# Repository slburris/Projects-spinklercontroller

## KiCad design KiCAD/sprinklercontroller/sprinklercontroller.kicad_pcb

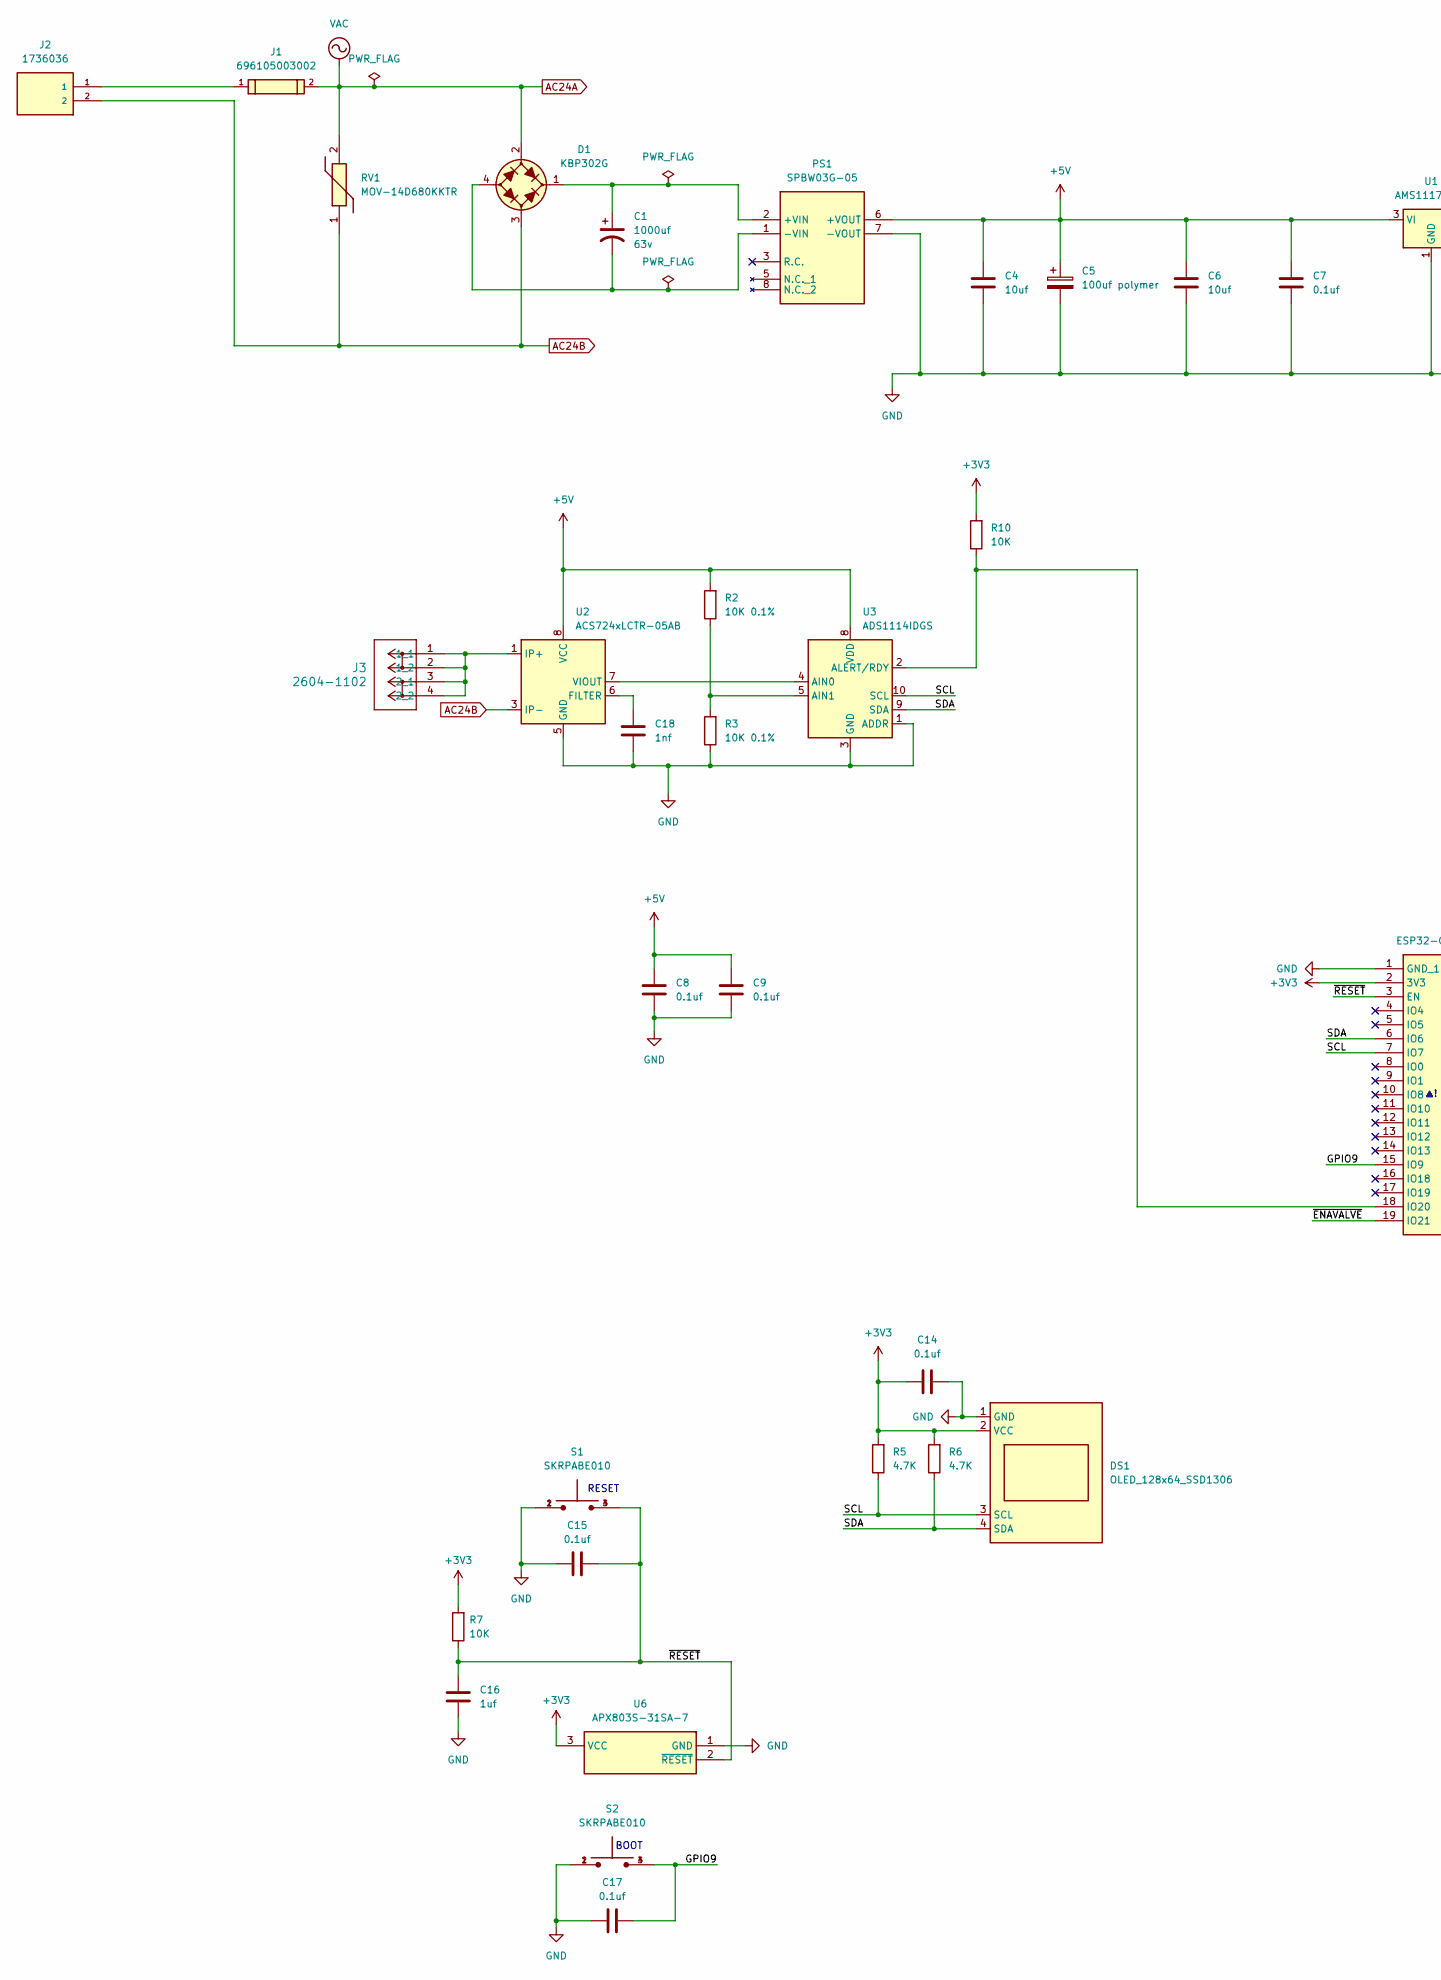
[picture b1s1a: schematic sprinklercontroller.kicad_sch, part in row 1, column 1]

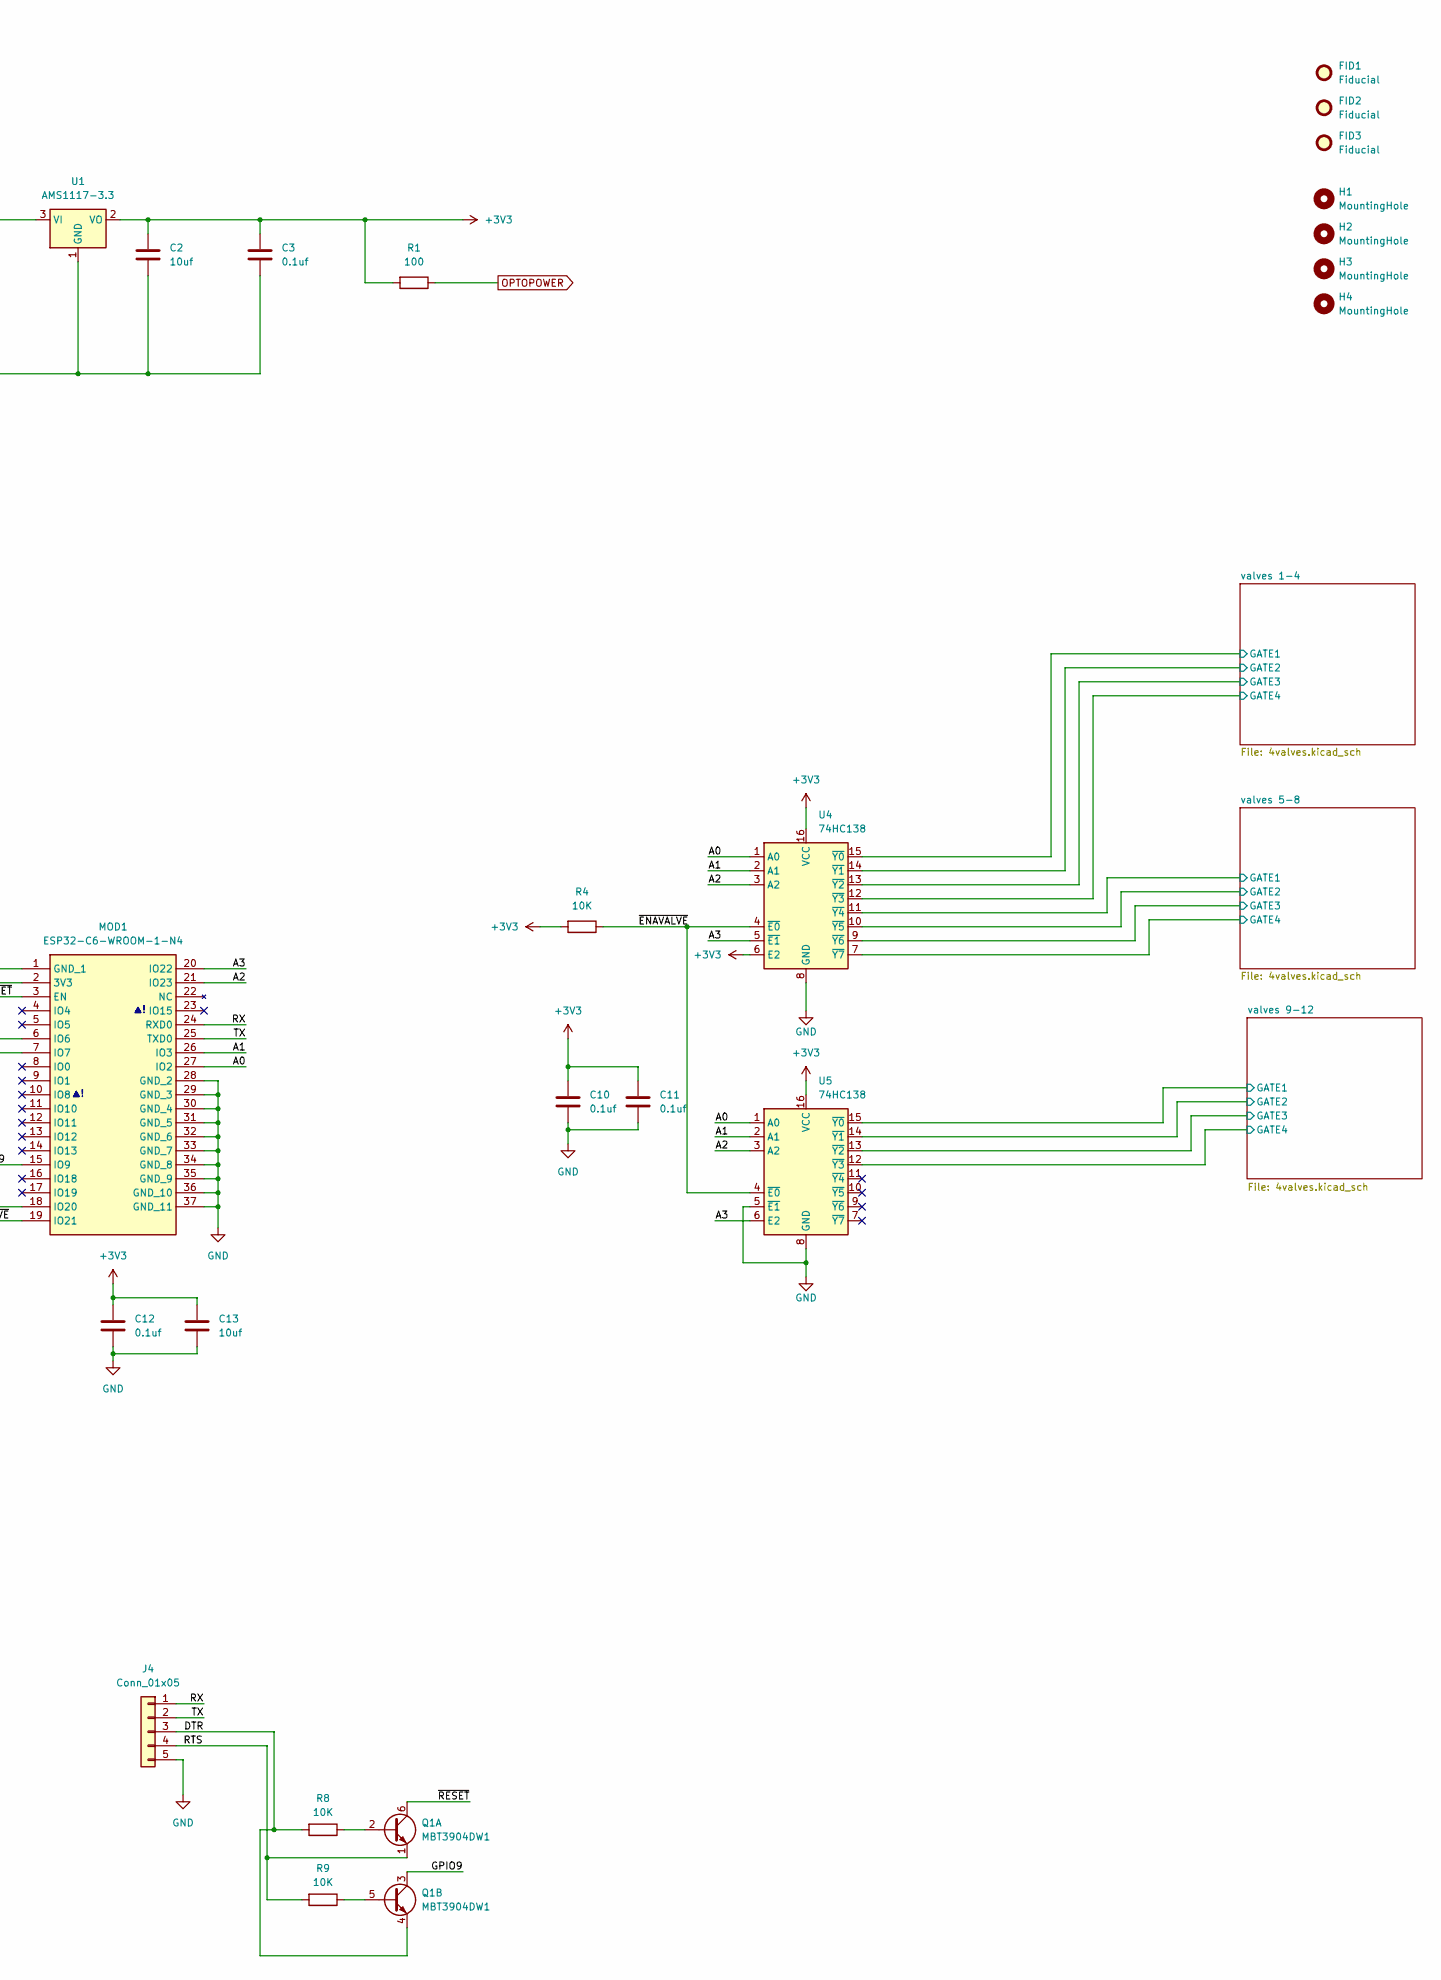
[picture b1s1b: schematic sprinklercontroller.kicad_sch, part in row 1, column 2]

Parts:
C1: 1000uf; CP_Radial_D16.0mm_P7.50mm; Voltage 63v; Tolerance 100%
C2, C6, C13: 10uf; C_1206_3216Metric_Pad1.33x1.80mm_HandSolder; Part C2012X5R1V106K085AC
C3, C7, C8, C9, C10, C11, C12, C14, C15, C17: 0.1uf; C_0603_1608Metric_Pad1.08x0.95mm_HandSolder; Part CGA3E2X7R1H104K080AA
C4: 10uf; C_1206_3216Metric_Pad1.33x1.80mm_HandSolder
C5: 100uf polymer; CP_Radial_D5.0mm_P2.00mm
C16: 1uf; C_1206_3216Metric_Pad1.33x1.80mm_HandSolder
C18: 1nf; C_1206_3216Metric_Pad1.33x1.80mm_HandSolder; Part C2012X5R1V106K085AC
D1: KBP302G; Diode_Bridge_KBP
DS1: OLED_128x64_SSD1306
FID1, FID2, FID3: Fiducial; Fiducial_1mm_Mask2mm
H1, H2, H3, H4: MountingHole; MountingHole_3.2mm_M3
J1: 696105003002
J2: 1736036; PHOENIX_1736036
J3: 2604-1102; CONN2_2604-1102_WAG
J4: Conn_01x05; PinHeader_1x05_P2.54mm_Vertical
MOD1: ESP32-C6-WROOM-1-N4; ESP32C6WROOM1N4; Manufacturer_Part_Number ESP32-C6-WROOM-1-N4; Mouser Part Number 356-ESP32C6WROOM1N4
PS1: SPBW03G-05; SPBW03G05; Manufacturer_Part_Number SPBW03G-05; Mouser Part Number 709-SPBW03G-05
Q1: MBT3904DW1; SOT-363_SC-70-6
R1: 100; R_1206_3216Metric_Pad1.42x1.75mm_HandSolder
R2, R3: 10K 0.1%; R_1206_3216Metric_Pad1.42x1.75mm_HandSolder
R4, R10: 10K; R_1206_3216Metric_Pad1.42x1.75mm_HandSolder
R5, R6: 4.7K; R_1206_3216Metric_Pad1.42x1.75mm_HandSolder
R7, R8, R9: 10K; R_1206_3216Metric_Pad1.30x1.75mm_HandSolder
RV1: MOV-14D680KKTR; MOV14D680KKTR; Manufacturer_Part_Number MOV-14D680KKTR; Mouser Part Number 652-MOV-14D680KKTR
S1, S2: SKRPABE010; SW_SKRPABE010
U1: AMS1117-3.3; SOT-223-3_TabPin2
U2: ACS724xLCTR-05AB; SOIC-8_3.9x4.9mm_P1.27mm
U3: ADS1114IDGS; TSSOP-10_3x3mm_P0.5mm
U4, U5: 74HC138; SOIC-16_3.9x9.9mm_P1.27mm
U6: APX803S-31SA-7; SOT96P240X100-3N; Mouser Part Number 621-APX803S-31SA-7

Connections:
+3V3: C2.1, C3.1, C10.2, C11.2, C12.2, C13.1, C14.2, DS1.2 (VCC), MOD1.2 (3V3), R1.2, R4.2, R5.2, R6.2, R7.2, R10.2, U1.2 (VO), U4.6 (E2), U4.16 (VCC), U5.16 (VCC), U6.3 (VCC)
+5V: C4.1, C5.1, C6.1, C7.1, C8.2, C9.2, PS1.6 (+VOUT), R2.2, U1.3 (VI), U2.8 (VCC), U3.8 (VDD)
/A0: MOD1.27 (IO2), U4.1 (A0), U5.1 (A0)
/A1: MOD1.26 (IO3), U4.2 (A1), U5.2 (A1)
/A2: MOD1.21 (IO23), U4.3 (A2), U5.3 (A2)
/A3: MOD1.20 (IO22), U4.5 (~E1), U5.6 (E2)
/DTR: J4.3, Q1.4 (E2), R8.2
/GPIO9: C17.2, MOD1.15 (IO9), Q1.3 (C2), S2.3, S2.4
/RTS: J4.4, Q1.1 (E1), R9.2
/RX: J4.1, MOD1.24 (RXD0)
/SCL: DS1.3 (SCL), MOD1.7 (IO7), R5.1, U3.10 (SCL)
/SDA: DS1.4 (SDA), MOD1.6 (IO6), R6.1, U3.9 (SDA)
/TX: J4.2, MOD1.25 (TXD0)
/valves 1-4/GATE1: U4.15 (~Y0); also elsewhere on the board
/valves 1-4/GATE2: U4.14 (~Y1); also elsewhere on the board
/valves 1-4/GATE3: U4.13 (~Y2); also elsewhere on the board
/valves 1-4/GATE4: U4.12 (~Y3); also elsewhere on the board
/valves 5-8/GATE1: U4.11 (~Y4); also elsewhere on the board
/valves 5-8/GATE2: U4.10 (~Y5); also elsewhere on the board
/valves 5-8/GATE3: U4.9 (~Y6); also elsewhere on the board
/valves 5-8/GATE4: U4.7 (~Y7); also elsewhere on the board
/valves 9-12/GATE1: U5.15 (~Y0); also elsewhere on the board
/valves 9-12/GATE2: U5.14 (~Y1); also elsewhere on the board
/valves 9-12/GATE3: U5.13 (~Y2); also elsewhere on the board
/valves 9-12/GATE4: U5.12 (~Y3); also elsewhere on the board
/~ENAVALVE: MOD1.19 (IO21), R4.1, U4.4 (~E0), U5.4 (~E0)
/~RESET: C15.2, C16.1, MOD1.3 (EN), Q1.6 (C1), R7.1, S1.3, S1.4, U6.2 (~RESET)
AC24A: D1.2 (1), J1.2, RV1.2; also elsewhere on the board
AC24B: D1.3 (2), J2.2, RV1.1, U2.3 (IP-), U2.4 (IP-); also elsewhere on the board
GND: C2.2, C3.2, C4.2, C5.2, C6.2, C7.2, C8.1, C9.1, C10.1, C11.1, C12.1, C13.2, C14.1, C15.1, C16.2, C17.1, C18.2, DS1.1 (GND), J4.5, MOD1.1 (GND_1), MOD1.28 (GND_2), MOD1.29 (GND_3), MOD1.30 (GND_4), MOD1.31 (GND_5), MOD1.32 (GND_6), MOD1.33 (GND_7), MOD1.34 (GND_8), MOD1.35 (GND_9), MOD1.36 (GND_10), MOD1.37 (GND_11), PS1.7 (-VOUT), R3.1, S1.1, S1.2, S2.1, S2.2, U1.1 (GND), U2.5 (GND), U3.1 (ADDR), U3.3 (GND), U4.8 (GND), U5.5 (~E1), U5.8 (GND), U6.1 (GND)
unnamed: C1.1, D1.1 (+), PS1.2 (+VIN)
unnamed: C1.2, D1.4 (-), PS1.1 (-VIN)
unnamed: J1.1, J2.1
unnamed: J3.1 (1_1), J3.2 (1_2), J3.3 (2_1), J3.4 (2_2), U2.1 (IP+), U2.2 (IP+)
unnamed: MOD1.18 (IO20), R10.1, U3.2 (ALERT/RDY)
unnamed: Q1.2 (B1), R8.1
unnamed: Q1.5 (B2), R9.1
unnamed: C18.1, U2.6 (FILTER)
unnamed: U2.7 (VIOUT), U3.4 (AIN0)
unnamed: R2.1, R3.2, U3.5 (AIN1)
OPTOPOWER: R1.1; also elsewhere on the board

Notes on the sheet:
RESET
BOOT

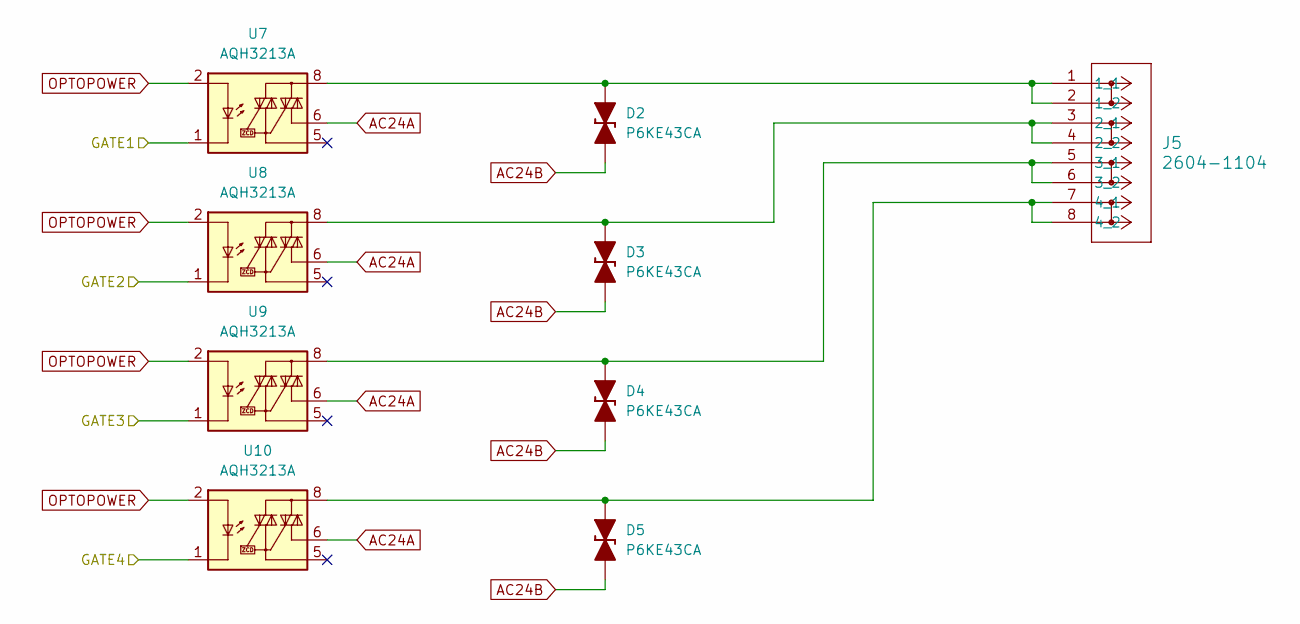
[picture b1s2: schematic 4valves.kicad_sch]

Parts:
D2, D3, D4, D5: P6KE43CA; D_DO-27_P5.08mm_Vertical_KathodeUp
J5: 2604-1104; CONN4_2604-1104_WAG
U7, U8, U9, U10: AQH3213A; SSO-7-8_6.4x9.78mm_P2.54mm

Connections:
/valves 1-4/GATE1: U7.1, U7.3, U7.4; also elsewhere on the board
/valves 1-4/GATE2: U8.1, U8.3, U8.4; also elsewhere on the board
/valves 1-4/GATE3: U9.1, U9.3, U9.4; also elsewhere on the board
/valves 1-4/GATE4: U10.1, U10.3, U10.4; also elsewhere on the board
AC24A: U7.6, U8.6, U9.6, U10.6; also elsewhere on the board
AC24B: D2.1 (K), D3.1 (K), D4.1 (K), D5.1 (K); also elsewhere on the board
unnamed: D2.2 (A), J5.1 (1_1), J5.2 (1_2), U7.8
unnamed: D3.2 (A), J5.3 (2_1), J5.4 (2_2), U8.8
unnamed: D4.2 (A), J5.5 (3_1), J5.6 (3_2), U9.8
unnamed: D5.2 (A), J5.7 (4_1), J5.8 (4_2), U10.8
OPTOPOWER: U7.2, U8.2, U9.2, U10.2; also elsewhere on the board

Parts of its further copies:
D6, D7, D8, D9, D10, D11, D12, D13: P6KE43CA; D_DO-27_P5.08mm_Vertical_KathodeUp
J6, J7: 2604-1104; CONN4_2604-1104_WAG
U11, U12, U13, U14, U15, U16, U17, U18: AQH3213A; SSO-7-8_6.4x9.78mm_P2.54mm

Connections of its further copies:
/valves 5-8/GATE1: U11.1, U11.3, U11.4; also elsewhere on the board
/valves 5-8/GATE2: U12.1, U12.3, U12.4; also elsewhere on the board
/valves 5-8/GATE3: U13.1, U13.3, U13.4; also elsewhere on the board
/valves 5-8/GATE4: U14.1, U14.3, U14.4; also elsewhere on the board
/valves 9-12/GATE1: U15.1, U15.3, U15.4; also elsewhere on the board
/valves 9-12/GATE2: U16.1, U16.3, U16.4; also elsewhere on the board
/valves 9-12/GATE3: U17.1, U17.3, U17.4; also elsewhere on the board
/valves 9-12/GATE4: U18.1, U18.3, U18.4; also elsewhere on the board
AC24A: U11.6, U12.6, U13.6, U14.6, U15.6, U16.6, U17.6, U18.6; also elsewhere on the board
AC24B: D6.1 (K), D7.1 (K), D8.1 (K), D9.1 (K), D10.1 (K), D11.1 (K), D12.1 (K), D13.1 (K); also elsewhere on the board
unnamed: D6.2 (A), J6.1 (1_1), J6.2 (1_2), U11.8
unnamed: D7.2 (A), J6.3 (2_1), J6.4 (2_2), U12.8
unnamed: D8.2 (A), J6.5 (3_1), J6.6 (3_2), U13.8
unnamed: D9.2 (A), J6.7 (4_1), J6.8 (4_2), U14.8
unnamed: D10.2 (A), J7.1 (1_1), J7.2 (1_2), U15.8
unnamed: D11.2 (A), J7.3 (2_1), J7.4 (2_2), U16.8
unnamed: D12.2 (A), J7.5 (3_1), J7.6 (3_2), U17.8
unnamed: D13.2 (A), J7.7 (4_1), J7.8 (4_2), U18.8
OPTOPOWER: U11.2, U12.2, U13.2, U14.2, U15.2, U16.2, U17.2, U18.2; also elsewhere on the board

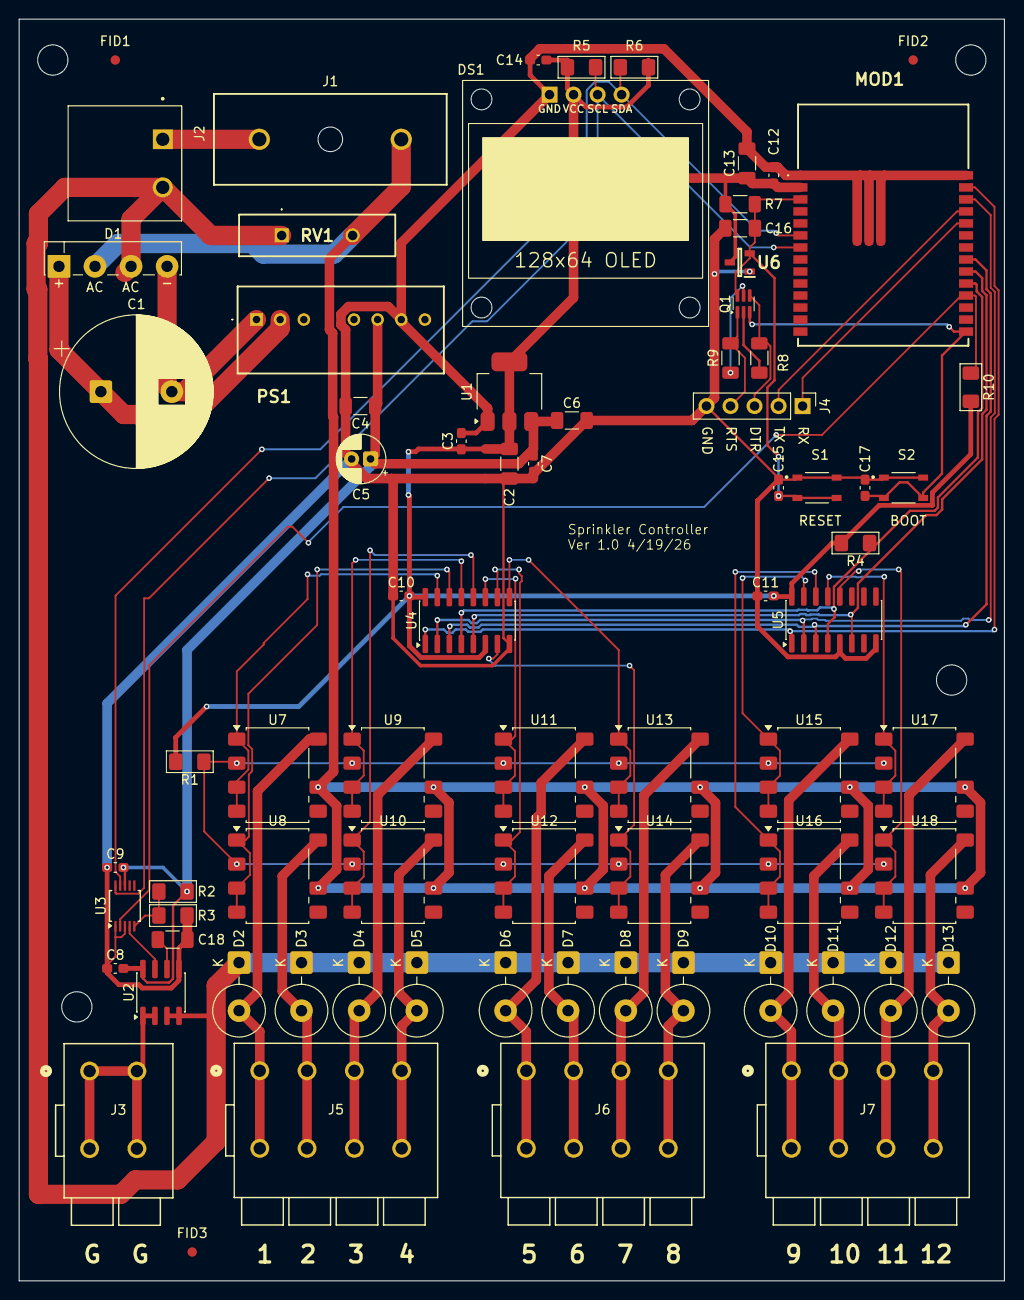
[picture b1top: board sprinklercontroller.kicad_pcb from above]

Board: 2 copper layers, 104.1 x 133.4 mm, 80 parts (0 on the bottom side), 53 nets.

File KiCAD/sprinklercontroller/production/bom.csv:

Designator,Footprint,Quantity,Value,LCSC Part #
C1,CP_Radial_D16.0mm_P7.50mm,1,1000uf,
"C10, C11, C12, C14, C15, C17, C3, C7, C8, C9",0603,10,0.1uf,
"C13, C2, C4, C6",1206,4,10uf,
C16,1206,1,1uf,
C18,1206,1,1nf,
C5,CP_Radial_D5.0mm_P2.00mm,1,100uf polymer,
D1,Diode_Bridge_KBP,1,KBP302G,
"D10, D11, D12, D13, D2, D3, D4, D5, D6, D7, D8, D9",D_DO-27_P5.08mm_Vertical_KathodeUp,12,P6KE43CA,
DS1,OLED_128x64_SSD1306,1,OLED_128x64_SSD1306,
"FID1, FID2, FID3",Fiducial_1mm_Mask2mm,3,Fiducial,
"H1, H2, H3, H4",MountingHole_3.2mm_M3,4,MountingHole,
J1,696105003002,1,696105003002,
J2,PHOENIX_1736036,1,1736036,
J3,CONN2_2604-1102_WAG,1,2604-1102,
J4,PinHeader_1x05_P2.54mm_Vertical,1,Conn_01x05,
"J5, J6, J7",CONN4_2604-1104_WAG,3,2604-1104,
MOD1,ESP32C6WROOM1N4,1,ESP32-C6-WROOM-1-N4,
PS1,SPBW03G05,1,SPBW03G-05,
Q1,SOT-363_SC-70-6,1,MBT3904DW1,
R1,1206,1,100,
"R10, R4, R7, R8, R9",1206,5,10K,
"R2, R3",1206,2,10K 0.1%,
"R5, R6",1206,2,4.7K,
RV1,MOV14D680KKTR,1,MOV-14D680KKTR,
"S1, S2",SW_SKRPABE010,2,SKRPABE010,
U1,SOT-223-3_TabPin2,1,AMS1117-3.3,
"U10, U11, U12, U13, U14, U15, U16, U17, U18, U7, U8, U9",SSO-7-8_6.4x9.78mm_P2.54mm,12,AQH3213A,
U2,SOIC-8_3.9x4.9mm_P1.27mm,1,ACS724xLCTR-05AB,
U3,TSSOP-10_3x3mm_P0.5mm,1,ADS1114IDGS,
"U4, U5",SOIC-16_3.9x9.9mm_P1.27mm,2,74HC138,
U6,SOT96P240X100-3N,1,APX803S-31SA-7,

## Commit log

2026-05-02 version 1.0 with solid state relays
